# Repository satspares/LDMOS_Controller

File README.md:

# LDMOS_Controller
LDMOS Controller with DWIN Display
New October 2026

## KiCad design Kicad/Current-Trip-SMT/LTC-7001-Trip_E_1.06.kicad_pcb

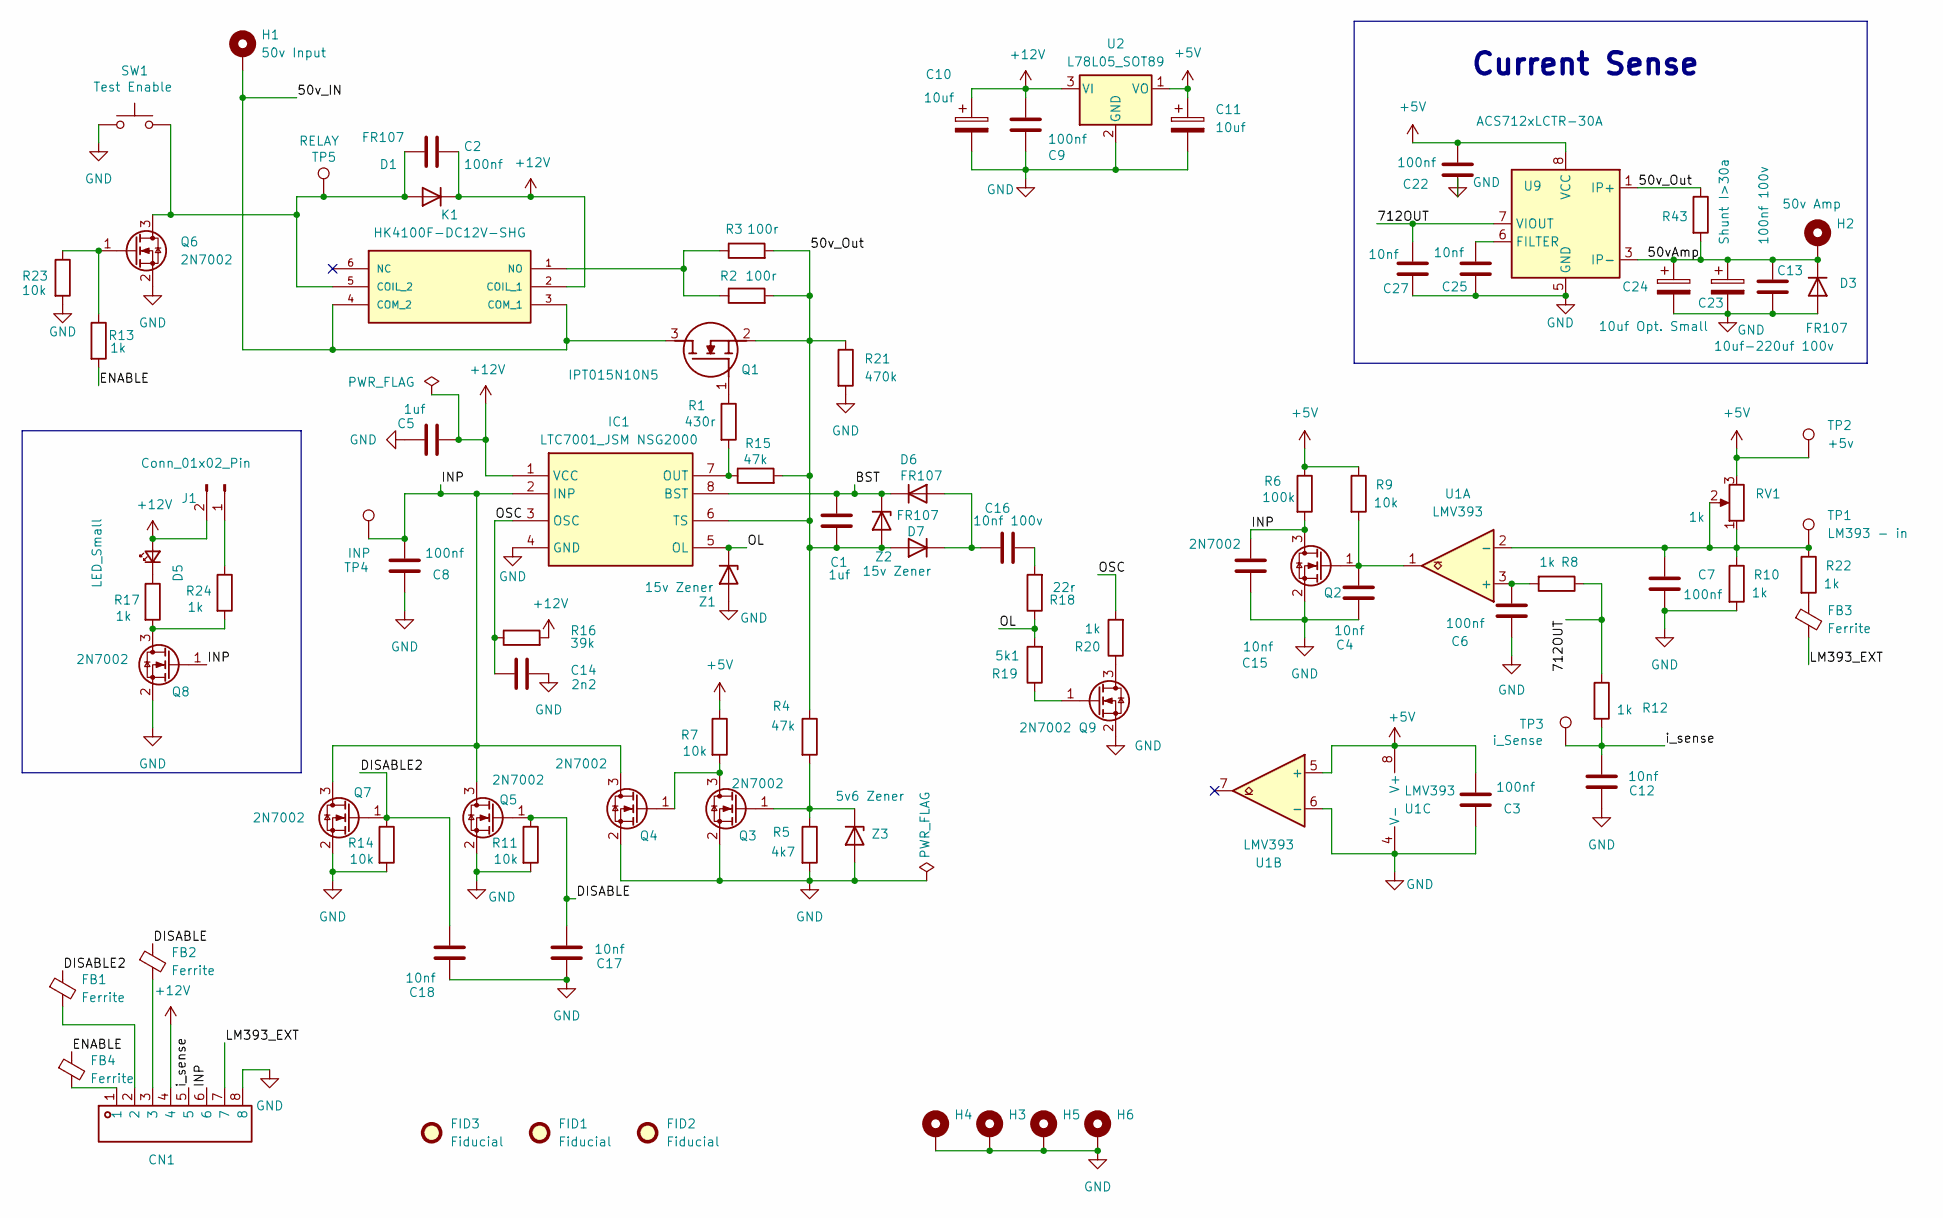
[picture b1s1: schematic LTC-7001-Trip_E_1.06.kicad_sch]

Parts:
C1, C5: 1uf; R_1206_3216Metric_Pad1.30x1.75mm_HandSolder
C2, C3, C6, C7, C8, C9, C22: 100nf; R_1206_3216Metric_Pad1.30x1.75mm_HandSolder
C4, C12, C15, C17, C18, C25, C27: 10nf; R_1206_3216Metric_Pad1.30x1.75mm_HandSolder
C10, C11: 10uf; R_1206_3216Metric_Pad1.30x1.75mm_HandSolder
C13: 100nf 100v; R_1206_3216Metric_Pad1.30x1.75mm_HandSolder
C14: 2n2; R_1206_3216Metric_Pad1.30x1.75mm_HandSolder
C16: 10nf 100v; R_1206_3216Metric_Pad1.30x1.75mm_HandSolder
C23: 10uf-220uf 100v; CP_Radial_D10.0mm_P5.00mm
C24: 10uf Opt. Small; CP_Radial_D8.0mm_P2.50mm
CN1: CONN-TH_8P-P2.54_KF141R-2.54-8P; Manufacturer Part KF141R-2.54-8P; LCSC Part Name 1x6P 2.54mm 每排P数:8 排数:1
D1, D3, D6, D7: FR107; D_SOD-123F-Mod
D5: LED_Small; LED_D3.0mm
FB1, FB2, FB3, FB4: Ferrite; R_1206_3216Metric_Pad1.30x1.75mm_HandSolder
FID1, FID2, FID3: Fiducial; Fiducial_0.75mm_Mask1.5mm
H1: 50v Input; Power-Pad
H2: 50v Amp; Power-Pad
H3, H4, H5, H6: MountingHole_Pad; MountingHole_3.5mm_Pad_Via
IC1: LTC7001_JSM NSG2000; SOIC-8_3.9x4.9mm_P1.27mm; Manufacturer_Part_Number JSMSEMI LTC7001IMSE-JSM
J1: Conn_01x02_Pin; JST_EH_B2B-EH-A_1x02_P2.50mm_Vertical
K1: HK4100F-DC12V-SHG; HK4100FDC5VSHG; MANUFACTURER_PART_NUMBER HK4100F-DC5V-SHG
Q1: IPT015N10N5; IPT015N10N5ATMA1; Manufacturer_Part_Number IPT015N10N5; Mouser Part Number 726-IPT015N10N5ATMA1
Q2, Q3, Q4, Q5, Q6, Q7, Q8, Q9: 2N7002; SOT-23-Mod2
R1: 430r; R_1206_3216Metric_Pad1.30x1.75mm_HandSolder
R2, R3: 100r; RESC11050X120N_Mod
R4, R15: 47k; R_1206_3216Metric_Pad1.30x1.75mm_HandSolder
R5: 4k7; R_1206_3216Metric_Pad1.30x1.75mm_HandSolder
R6: 100k; R_1206_3216Metric_Pad1.30x1.75mm_HandSolder
R7, R9, R11, R14, R23: 10k; R_1206_3216Metric_Pad1.30x1.75mm_HandSolder
R8, R10, R12, R13, R17, R20, R22, R24: 1k; R_1206_3216Metric_Pad1.30x1.75mm_HandSolder
R16: 39k; R_1206_3216Metric_Pad1.30x1.75mm_HandSolder
R18: 22r; R_1206_3216Metric_Pad1.30x1.75mm_HandSolder
R19: 5k1; R_1206_3216Metric_Pad1.30x1.75mm_HandSolder
R21: 470k; R_1206_3216Metric_Pad1.30x1.75mm_HandSolder
R43: Shunt I>30a; RESC11050X120N-hole
RV1: 1k; Potentiometer_Bourns_3266W_Vertical
SW1: Test Enable; SW_PUSH_6mm
TP1: LM393 - in; TestPoint_THTPad_3.0x3.0mm_Drill1.5mm
TP2: +5v; TestPoint_THTPad_3.0x3.0mm_Drill1.5mm
TP3: i_Sense; TestPoint_THTPad_3.0x3.0mm_Drill1.5mm
TP4: INP; TestPoint_THTPad_3.0x3.0mm_Drill1.5mm
TP5: RELAY; TestPoint_THTPad_3.0x3.0mm_Drill1.5mm
U1: LMV393; SOP-8_3.76x4.96mm_P1.27mm
U2: L78L05_SOT89; SOT-89-3_Handsoldering
U9: ACS712xLCTR-30A; SOIC-8_3.9x4.9mm_P1.27mm
Z1, Z2: 15v Zener; D_SOD-123F-Mod
Z3: 5v6 Zener; D_SOD-123F-Mod

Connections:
+5V: C3.2, C11.1, C22.1, R6.1, R7.1, R9.1, RV1.3, TP2.1 (1_1), U1.5 (+), U1.8 (V+), U2.1 (VO), U9.8 (VCC)
+12V: C2.2, C5.2, C9.2, C10.1, CN1.4, D1.1 (K), D5.2 (A), IC1.1 (VCC), J1.2, K1.2 (COIL_1), R16.2, U2.3 (VI)
/50vAmp: C13.1, C23.1, C24.1, D3.1 (K), H2.1 (1_1), R43.2, U9.3 (IP-), U9.4 (IP-)
/50v_IN: H1.1 (1_1), K1.3 (COM_1), K1.4 (COM_2), Q1.3 (S)
/50v_Out: C1.2, D7.2 (A), IC1.6 (TS), Q1.2 (D), R2.2, R3.2, R4.1, R15.2, R21.1, R43.1, U9.1 (IP+), U9.2 (IP+), Z2.2 (A)
/712OUT: C27.1, R8.1, R12.1, U9.7 (VIOUT)
/BST: C1.1, D6.1 (K), IC1.8 (BST), Z2.1 (K)
/DISABLE: C17.2, FB2.1, Q5.1 (G), R11.1
/DISABLE2: C18.2, FB1.1, Q7.1 (G), R14.1
/ENABLE: FB4.1, R13.2
/INP: C8.2, C15.1, CN1.6, IC1.2 (INP), Q2.3 (D), Q4.3 (D), Q5.3 (D), Q7.3 (D), Q8.1 (G), R6.2, TP4.1 (1_1)
/LM393_EXT: CN1.7, FB3.2
/OL: IC1.5 (OL), R18.1, R19.2, Z1.1 (K)
/OSC: C14.1, IC1.3 (OSC), R16.1, R20.2
/i_sense: C12.1, CN1.5, R12.2, TP3.1 (1_1)
GND: C3.1, C4.1, C5.1, C6.1, C7.1, C8.1, C9.1, C10.2, C11.2, C12.2, C13.2, C14.2, C15.2, C17.1, C18.1, C22.2, C23.2, C24.2, C25.1, C27.2, CN1.8, D3.2 (A), H3.1 (1_1), H4.1 (1_1), H5.1 (1_1), H6.1 (1_1), IC1.4 (GND), Q2.2 (S), Q3.2 (S), Q4.2 (S), Q5.2 (S), Q6.2 (S), Q7.2 (S), Q8.2 (S), Q9.2 (S), R5.2, R10.2, R11.2, R14.2, R21.2, R23.2, SW1.1, U1.4 (V-), U1.6 (-), U2.2 (GND), U9.5 (GND), Z1.2 (A), Z3.2 (A)
unnamed: C16.2, R18.2
unnamed: CN1.1, FB4.2
unnamed: CN1.2, FB1.2
unnamed: CN1.3, FB2.2
unnamed: C2.1, D1.2 (A), K1.5 (COIL_2), Q6.3 (D), SW1.2, TP5.1 (1_1)
unnamed: D5.1 (K), R17.1
unnamed: C16.1, D6.2 (A), D7.1 (K)
unnamed: FB3.1, R22.2
unnamed: IC1.7 (OUT), R1.2, R15.1
unnamed: J1.1, R24.1
unnamed: K1.1 (NO), R2.1, R3.1
unnamed: Q1.1 (G), R1.1
unnamed: C4.2, Q2.1 (G), R9.2, U1.1
unnamed: Q3.3 (D), Q4.1 (G), R7.2
unnamed: Q3.1 (G), R4.2, R5.1, Z3.1 (K)
unnamed: Q6.1 (G), R13.1, R23.1
unnamed: Q8.3 (D), R17.2, R24.2
unnamed: Q9.3 (D), R20.1
unnamed: Q9.1 (G), R19.1
unnamed: C6.2, R8.2, U1.3 (+)
unnamed: C7.2, R10.1, R22.1, RV1.1, RV1.2, TP1.1 (1_1), U1.2 (-)
unnamed: C25.2, U9.6 (FILTER)

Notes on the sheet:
Current Sense

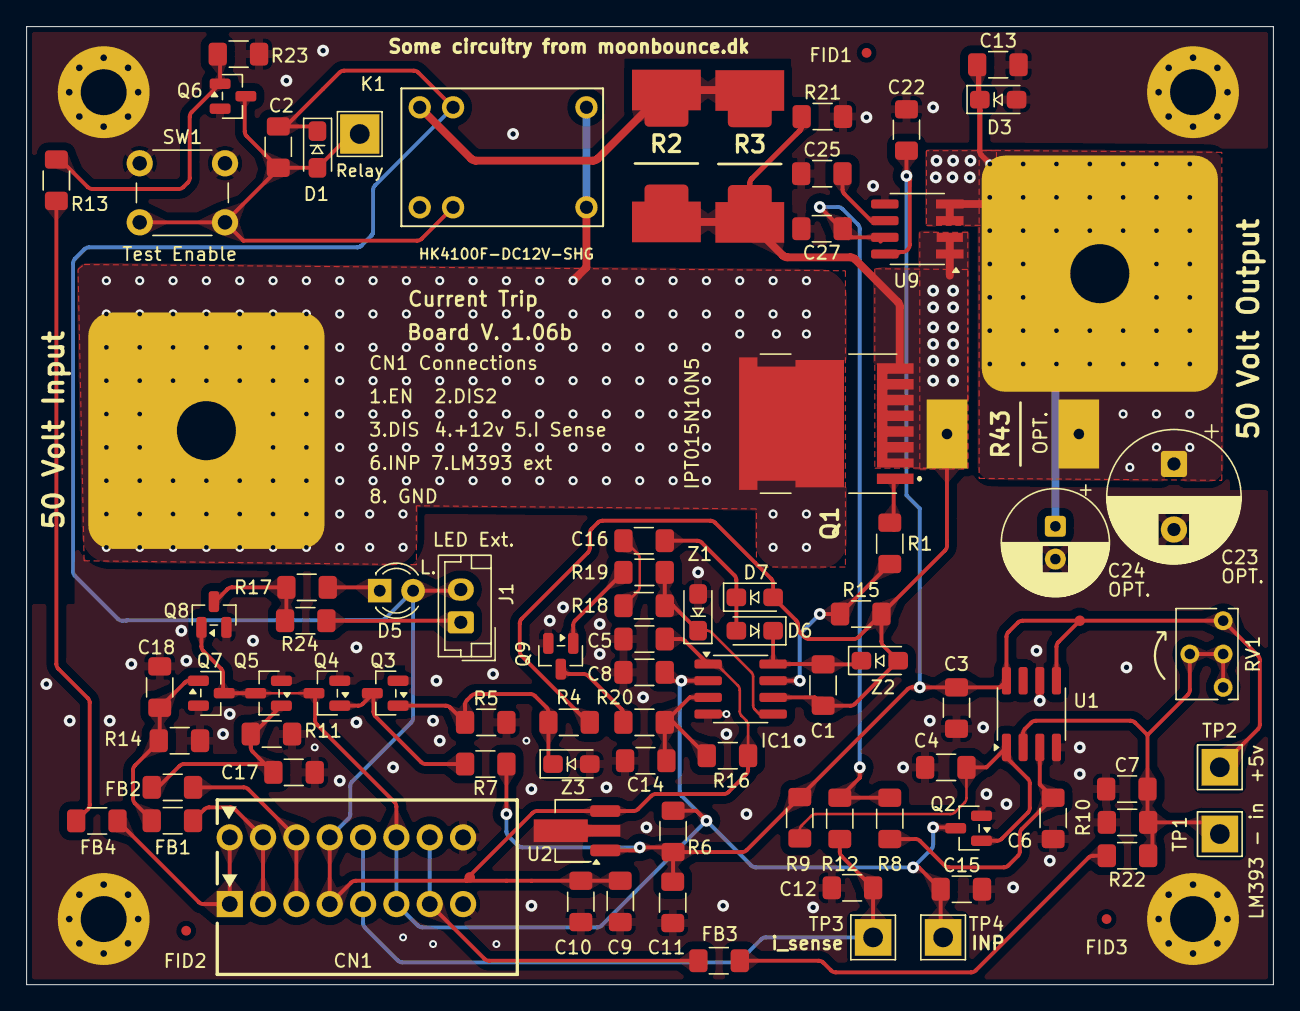
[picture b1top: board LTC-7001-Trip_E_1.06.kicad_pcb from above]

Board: 2 copper layers, 95.0 x 73.0 mm, 92 parts (0 on the bottom side), 38 nets.

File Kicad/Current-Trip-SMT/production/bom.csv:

Designator,Footprint,Quantity,Value,LCSC Part #
"C1, C5",1206,2,1uf,
"C10, C11",1206,2,10uf,
"C12, C15, C17, C18, C25, C27, C4",1206,7,10nf,
C13,1206,1,100nf 100v,
C14,1206,1,2n2,
C16,1206,1,10nf 100v,
"C2, C22, C3, C6, C7, C8, C9",1206,7,100nf,
C23,CP_Radial_D10.0mm_P5.00mm,1,10uf-220uf 100v,
C24,CP_Radial_D8.0mm_P2.50mm,1,10uf Opt. Small,
CN1,CONN-TH_8P-P2.54_KF141R-2.54-8P,1,~,
"D1, D3, D6, D7",D_SOD-123F-Mod,4,FR107,
D5,LED_D3.0mm,1,LED_Small,
"FB1, FB2, FB3, FB4",1206,4,Ferrite,
IC1,SOIC-8_3.9x4.9mm_P1.27mm,1,LTC7001_JSM NSG2000,
J1,JST_EH_B2B-EH-A_1x02_P2.50mm_Vertical,1,Conn_01x02_Pin,
K1,HK4100FDC5VSHG,1,HK4100F-DC12V-SHG,
Q1,IPT015N10N5ATMA1,1,IPT015N10N5,
"Q2, Q3, Q4, Q5, Q6, Q7, Q8, Q9",SOT-23-Mod2,8,2N7002,
R1,1206,1,430r,
"R10, R12, R13, R17, R20, R22, R24, R8",1206,8,1k,
"R11, R14, R23, R7, R9",1206,5,10k,
"R15, R4",1206,2,47k,
R16,1206,1,39k,
R18,1206,1,22r,
R19,1206,1,5k1,
"R2, R3",RESC11050X120N_Mod,2,100r,
R21,1206,1,470k,
R43,RESC11050X120N-hole,1,Shunt I>30a,
R5,1206,1,4k7,
R6,1206,1,100k,
RV1,Potentiometer_Bourns_3266W_Vertical,1,1k,
SW1,SW_PUSH_6mm,1,Test Enable,
TP1,TestPoint_THTPad_3.0x3.0mm_Drill1.5mm,1,LM393 - in,
TP2,TestPoint_THTPad_3.0x3.0mm_Drill1.5mm,1,+5v,
TP3,TestPoint_THTPad_3.0x3.0mm_Drill1.5mm,1,i_Sense,
TP4,TestPoint_THTPad_3.0x3.0mm_Drill1.5mm,1,INP,
TP5,TestPoint_THTPad_3.0x3.0mm_Drill1.5mm,1,RELAY,
U1,SOP-8_3.76x4.96mm_P1.27mm,1,LMV393,
U2,SOT-89-3_Handsoldering,1,L78L05_SOT89,
U9,SOIC-8_3.9x4.9mm_P1.27mm,1,ACS712xLCTR-30A,
"Z1, Z2",D_SOD-123F-Mod,2,15v Zener,
Z3,D_SOD-123F-Mod,1,5v6 Zener,

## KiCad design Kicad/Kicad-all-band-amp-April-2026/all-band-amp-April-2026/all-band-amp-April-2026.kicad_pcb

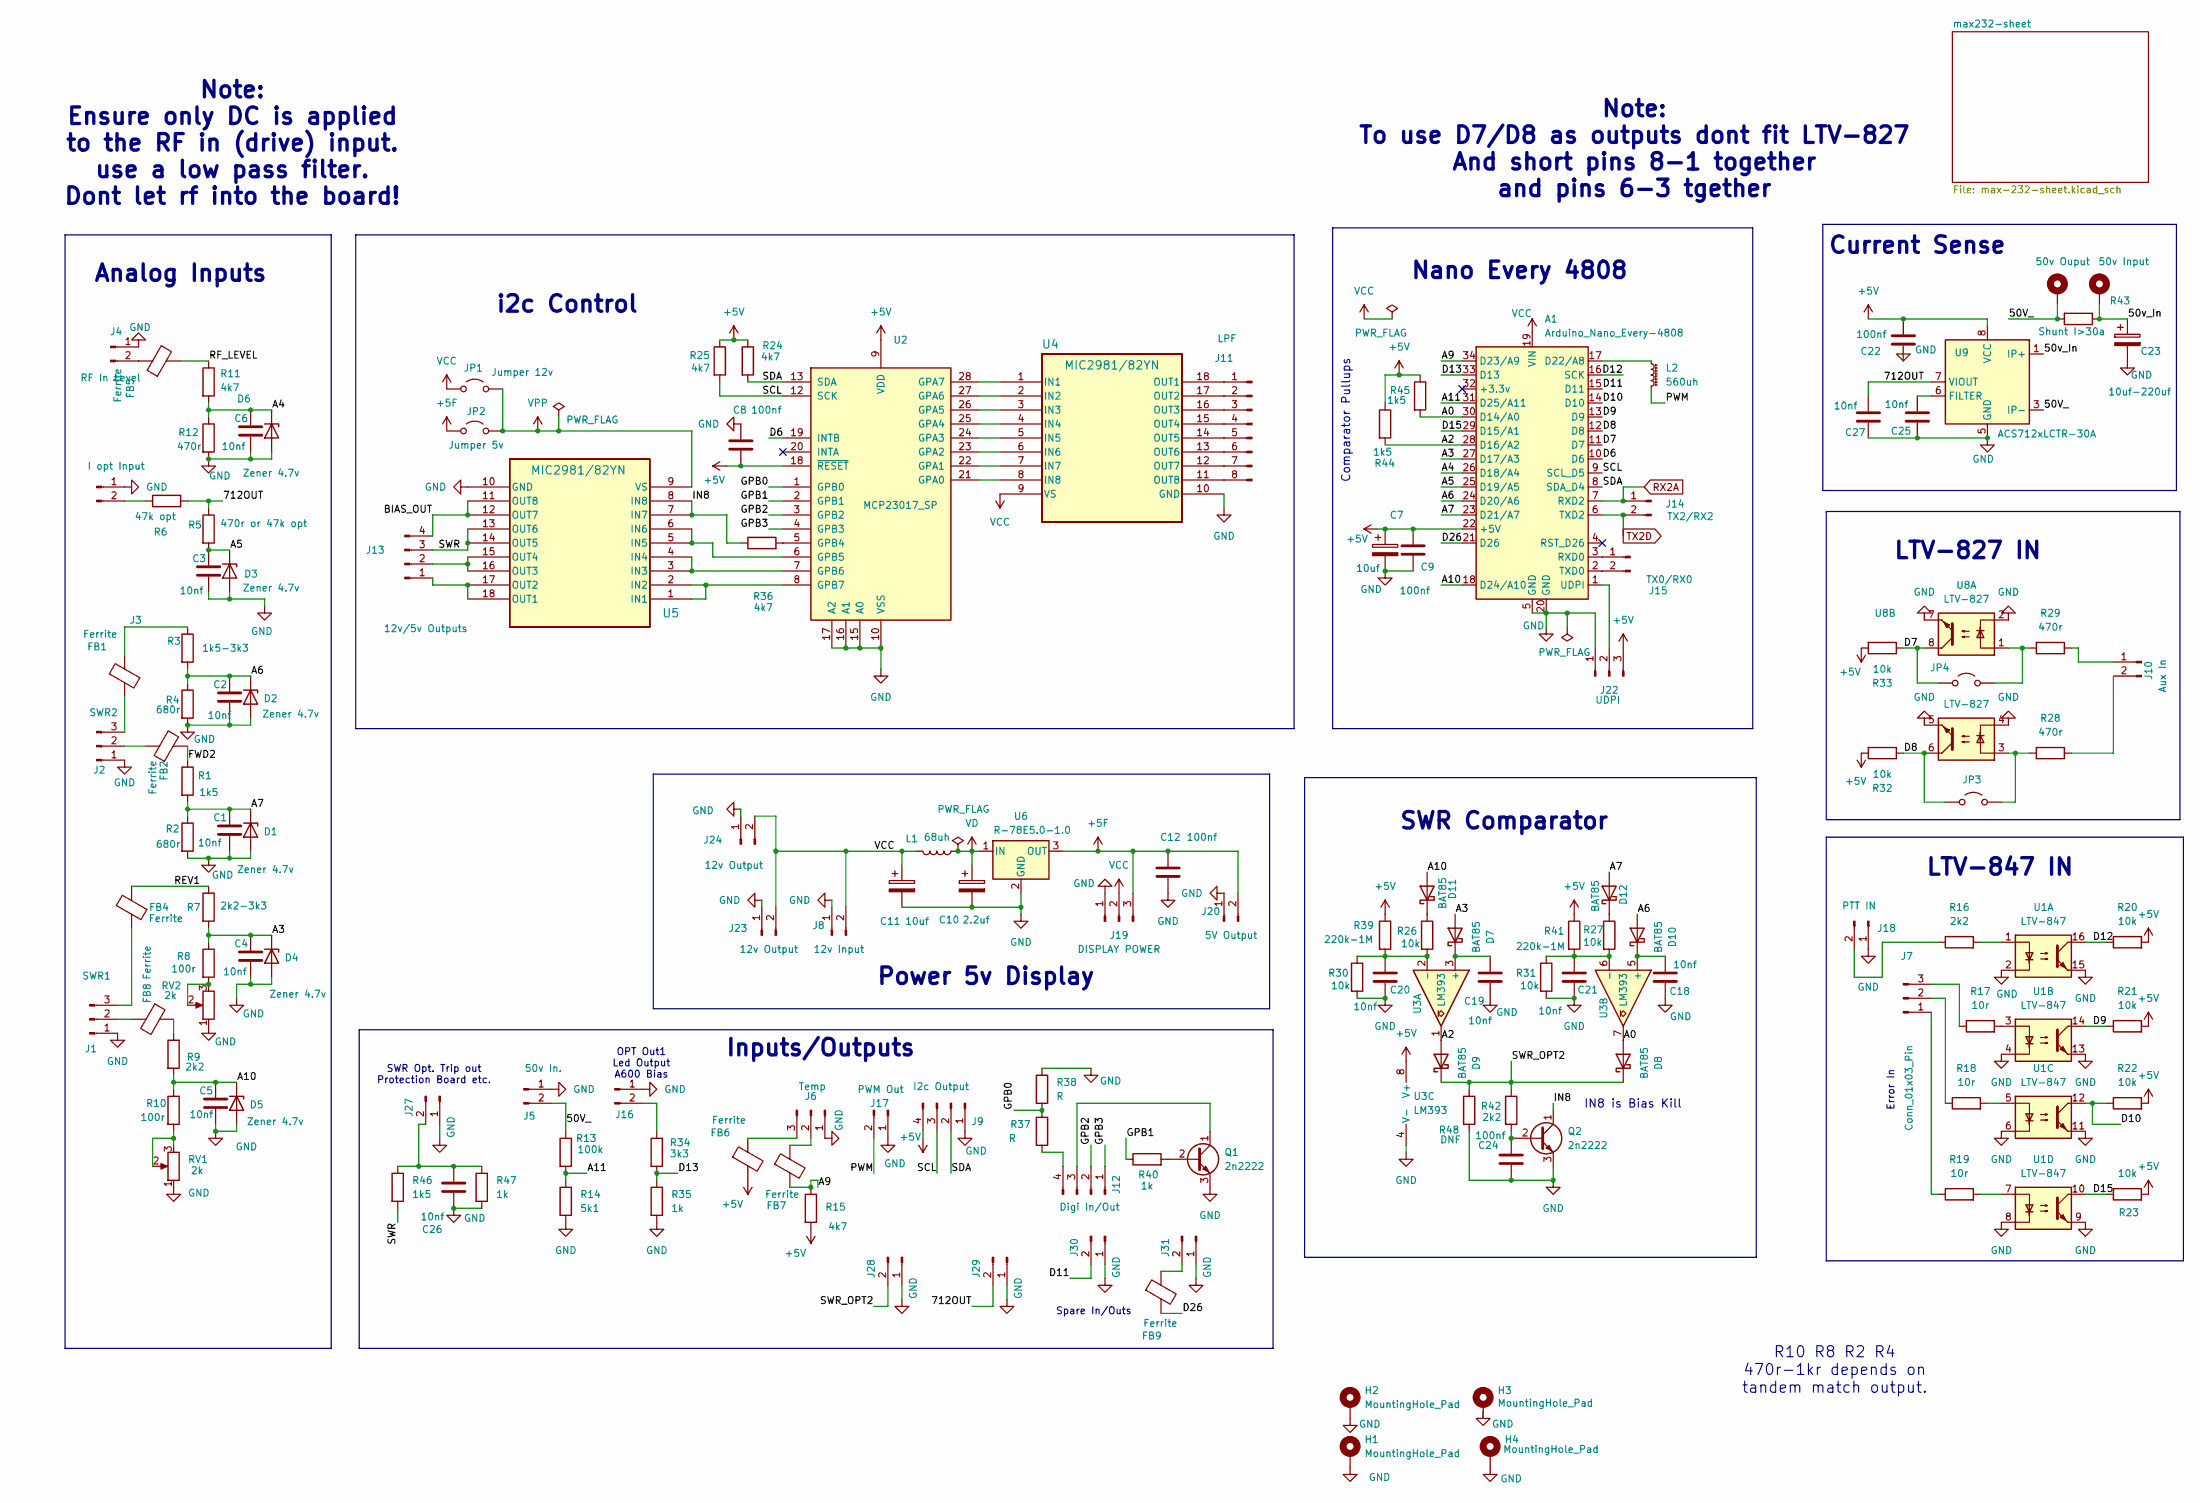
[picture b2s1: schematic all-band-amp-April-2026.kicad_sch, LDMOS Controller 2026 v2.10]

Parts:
A1: Arduino_Nano_Every-4808; DIP-34_W15.24mm
C1, C2, C3, C4, C5, C6, C18, C19, C20, C21, C25, C26, C27: 10nf; C_Disc_D3.4mm_W2.1mm_P2.50mm
C7, C11: 10uf; CP_Radial_D5.0mm_P2.00mm
C8, C9, C12, C22, C24: 100nf; C_Disc_D6.0mm_W2.5mm_P5.00mm
C10: 2.2uf; CP_Radial_D5.0mm_P2.00mm
C23: 10uf-220uf; CP_Radial_D10.0mm_P5.00mm
D1, D2, D3, D4, D5, D6: Zener 4.7v; D_DO-35_SOD27_P7.62mm_Horizontal
D7, D8, D9, D10, D11, D12: BAT85; D_DO-35_SOD27_P7.62mm_Horizontal
FB1, FB2, FB4, FB5, FB6, FB7, FB8, FB9: Ferrite; R_1206_3216Metric_Pad1.30x1.75mm_HandSolder-mod
H1, H2, H3, H4: MountingHole_Pad; MountingHole_3.5mm_Pad_Via
H5: 50v Ouput; PowerPad9mm
H6: 50v Input; PowerPad9mm
J1: SWR1; JST_EH_B3B-EH-A_1x03_P2.50mm_Vertical-mod2
J2: SWR2; JST_EH_B3B-EH-A_1x03_P2.50mm_Vertical-mod2
J3: I opt Input; JST_EH_B2B-EH-A_1x02_P2.50mm_Vertical-Mod
J4: RF In Level; JST_EH_B2B-EH-A_1x02_P2.50mm_Vertical-Mod
J5, J16: 50v In.; JST_EH_B2B-EH-A_1x02_P2.50mm_Vertical-Mod
J6: Temp; JST_EH_B3B-EH-A_1x03_P2.50mm_Vertical-mod2
J7: Conn_01x03_Pin; JST_EH_B3B-EH-A_1x03_P2.50mm_Vertical-mod2
J8: 12v Input; JST_EH_B2B-EH-A_1x02_P2.50mm_Vertical-Mod
J9: I2c Output; JST_EH_B4B-EH-A_1x04_P2.50mm_Vertical-mod2
J10: Aux In; JST_EH_B2B-EH-A_1x02_P2.50mm_Vertical-Mod
J11: LPF; JST_EH_B8B-EH-A_1x08_P2.50mm_Vertical
J12: Digi In/Out; JST_EH_B4B-EH-A_1x04_P2.50mm_Vertical-mod2
J13: 12v/5v Outputs; JST_EH_B4B-EH-A_1x04_P2.50mm_Vertical-mod2
J14: TX2/RX2; JST_EH_B2B-EH-A_1x02_P2.50mm_Vertical-Mod
J15: TX0/RX0; JST_EH_B2B-EH-A_1x02_P2.50mm_Vertical-Mod
J17: PWM Out; JST_EH_B2B-EH-A_1x02_P2.50mm_Vertical-Mod
J18: PTT IN; JST_EH_B2B-EH-A_1x02_P2.50mm_Vertical-Mod
J19: DISPLAY POWER; JST_EH_B3B-EH-A_1x03_P2.50mm_Vertical-mod2
J20: 5V Output; JST_EH_B2B-EH-A_1x02_P2.50mm_Vertical-Mod
J22: UDPI; JST_EH_B3B-EH-A_1x03_P2.50mm_Vertical
J23, J24: 12v Output; JST_EH_B2B-EH-A_1x02_P2.50mm_Vertical-Mod
J27, J28, J29, J30, J31: SWR trip out; JST_EH_B2B-EH-A_1x02_P2.50mm_Vertical-Mod
JP1: Jumper 12v; SolderWire-0.5sqmm_1x02_P4.8mm_D0.9mm_OD2.3mm
JP2: Jumper 5v; SolderWire-0.5sqmm_1x02_P4.8mm_D0.9mm_OD2.3mm
JP3, JP4: Jumper_2_Open; SolderJumper-2_P1.3mm_Open_TrianglePad1.0x1.5mm
L1: 68uh; L_Radial_D7.0mm_P3.00mm
L2: 560uh; L_Axial_L5.3mm_D2.2mm_P7.62mm_Horizontal_Vishay_IM-1
Q1, Q2: 2n2222; TO-92_HandSolder
R1, R44, R45, R46: 1k5; R_Axial_DIN0207_L6.3mm_D2.5mm_P7.62mm_Horizontal
R2, R4: 680r; R_Axial_DIN0207_L6.3mm_D2.5mm_P7.62mm_Horizontal
R3: 1k5-3k3; R_Axial_DIN0207_L6.3mm_D2.5mm_P7.62mm_Horizontal
R5: 470r or 47k opt; R_Axial_DIN0207_L6.3mm_D2.5mm_P7.62mm_Horizontal
R6: 47k opt; R_Axial_DIN0207_L6.3mm_D2.5mm_P7.62mm_Horizontal
R7: 2k2-3k3; R_Axial_DIN0207_L6.3mm_D2.5mm_P7.62mm_Horizontal
R8, R10: 100r; R_Axial_DIN0207_L6.3mm_D2.5mm_P7.62mm_Horizontal
R9, R16, R42: 2k2; R_Axial_DIN0207_L6.3mm_D2.5mm_P7.62mm_Horizontal
R11, R15, R24, R25, R36: 4k7; R_Axial_DIN0207_L6.3mm_D2.5mm_P7.62mm_Horizontal
R12, R28, R29: 470r; R_Axial_DIN0207_L6.3mm_D2.5mm_P7.62mm_Horizontal
R13: 100k; R_Axial_DIN0207_L6.3mm_D2.5mm_P7.62mm_Horizontal
R14: 5k1; R_Axial_DIN0207_L6.3mm_D2.5mm_P7.62mm_Horizontal
R17, R18, R19: 10r; R_Axial_DIN0207_L6.3mm_D2.5mm_P7.62mm_Horizontal
R20, R21, R22, R23, R26, R27, R30, R31, R32, R33: 10k; R_Axial_DIN0207_L6.3mm_D2.5mm_P7.62mm_Horizontal
R34: 3k3; R_Axial_DIN0207_L6.3mm_D2.5mm_P7.62mm_Horizontal
R35, R40, R47: 1k; R_Axial_DIN0207_L6.3mm_D2.5mm_P7.62mm_Horizontal
R37, R38: R; R_Axial_DIN0207_L6.3mm_D2.5mm_P7.62mm_Horizontal
R39, R41: 220k-1M; R_Axial_DIN0207_L6.3mm_D2.5mm_P7.62mm_Horizontal
R43: Shunt I>30a; CHSA3920R0003F-MOD
R48: DNF; R_Axial_DIN0207_L6.3mm_D2.5mm_P7.62mm_Horizontal
RV1, RV2: 2k; Potentiometer_Bourns_3299Y_Vertical
U1: LTV-847; DIP-16_W7.62mm
U2: MCP23017_SP; DIP-28_W7.62mm
U3: LM393; DIP-8_W7.62mm
U4, U5: MIC2981/82YN; DIP-18_W7.62mm_Socket
U6: R-78E5.0-1.0; Converter_DCDC_RECOM_R-78E-0.5_THT
U8: LTV-827; DIP-8_W7.62mm
U9: ACS712xLCTR-30A; SOIC-8_3.9x4.9mm_P1.27mm

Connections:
+5F: C12.1, J19.3, J20.2, JP2.1 (A), U6.3 (OUT); also elsewhere on the board
+5V: A1.22 (+5V), C7.1, C8.2, C9.1, C22.1, FB6.2, J9.4, J22.3, R15.2, R20.2, R21.2, R22.2, R23.2, R24.1, R25.1, R32.2, R33.2, R39.1, R41.1, R44.1, R45.1, U2.9 (VDD), U2.18 (~RESET), U3.8 (V+), U9.8 (VCC)
/50V_: H5.1 (1_1), J5.2, R13.1, R43.2, U9.3 (IP-), U9.4 (IP-)
/50v_In: C23.1, H6.1 (1_1), R43.1, U9.1 (IP+), U9.2 (IP+)
/712OUT: C27.1, J29.2, R5.1, R6.2, U9.7 (VIOUT)
/A0: A1.30 (D14/A0), D8.2 (A), R45.2, U3.7
/A2: A1.28 (D16/A2), D9.2 (A), R44.2, U3.1
/A3: A1.27 (D17/A3), C4.1, D4.1 (K), D7.2 (A), R7.2, R8.1
/A4: A1.26 (D18/A4), C6.1, D6.1 (K), R11.2, R12.1
/A5: A1.25 (D19/A5), C3.1, D3.1 (K), R5.2
/A6: A1.24 (D20/A6), C2.1, D2.1 (K), D10.2 (A), R3.2, R4.1
/A7: A1.23 (D21/A7), C1.1, D1.1 (K), D12.2 (A), R1.2, R2.1
/A9: A1.34 (D23/A9), FB7.2, R15.1
/A10: A1.18 (D24/A10), C5.1, D5.1 (K), D11.2 (A), R9.2, R10.1
/A11: A1.31 (D25/A11), R13.2, R14.1
/BIAS_OUT: J13.4, U5.11 (OUT8), U5.12 (OUT7)
/D6: A1.10 (D6), U2.19 (INTB)
/D7: A1.11 (D7), JP4.1 (A), R33.1, U8.8
/D8: A1.12 (D8), JP3.1 (A), R32.1, U8.6
/D9: A1.13 (D9), R21.1, U1.14
/D10: A1.14 (D10), R22.1, U1.12
/D11: A1.15 (D11), J30.2
/D12: A1.16 (SCK), R20.1, U1.16
/D13: A1.33 (D13), R34.2, R35.1
/D15: A1.29 (D15/A1), R23.1, U1.10
/D26: A1.21 (D26), FB9.2
/FWD2: FB2.2, R1.1
/GPB0: R37.1, R38.2, U2.1 (GPB0)
/GPB1: R40.1, U2.2 (GPB1)
/GPB2: J12.2, U2.3 (GPB2)
/GPB3: J12.1, U2.4 (GPB3)
/IN8: Q2.1 (C), R36.1, U5.7 (IN7), U5.8 (IN8)
/PWM: J17.2, L2.2
/REV1: FB4.2, R7.1
/RF_LEVEL: FB5.2, R11.1
/SCL: A1.9 (SCL_D5), J9.3, R25.2, U2.12 (SCK)
/SDA: A1.8 (SDA_D4), J9.2, R24.2, U2.13 (SDA)
/SWR: J13.3, R46.2, U5.13 (OUT6), U5.14 (OUT5)
/SWR_OPT2: D8.1 (K), D9.1 (K), J28.2, R42.1, R48.1
GND: A1.5 (GND), A1.20 (GND), C1.2, C2.2, C3.2, C4.2, C5.2, C6.2, C7.2, C8.1, C9.2, C10.2, C11.2, C12.2, C18.1, C19.2, C20.2, C21.2, C22.2, C23.2, C24.2, C25.1, C26.2, C27.2, D1.2 (A), D2.2 (A), D3.2 (A), D4.2 (A), D5.2 (A), D6.2 (A), H1.1 (1_1), H2.1 (1_1), H3.1 (1_1), H4.1 (1_1), J1.1, J2.1, J3.1, J4.1, J5.1, J6.1, J8.1, J9.1, J16.1, J17.1, J18.1, J19.1, J20.1, J22.1, J23.1, J24.1, J27.1, J28.1, J29.1, J30.1, J31.1, Q1.3 (E), Q2.3 (E), R2.2, R4.2, R12.2, R14.2, R30.2, R31.2, R35.2, R38.1, R47.2, R48.2, RV1.1, RV2.1, U1.2, U1.4, U1.6, U1.8, U1.9, U1.11, U1.13, U1.15, U2.10 (VSS), U2.15 (A0), U2.16 (A1), U2.17 (A2), U3.4 (V-), U4.10 (GND), U5.10 (GND), U6.2 (GND), U8.2, U8.4, U8.5, U8.7, U9.5 (GND); also elsewhere on the board
unnamed: A1.17 (D22/A8), L2.1
unnamed: A1.3 (RXD0), J15.1
unnamed: A1.2 (TXD0), J15.2
unnamed: A1.1 (UDPI), J22.2
unnamed: C19.1, D7.1 (K), U3.3 (+)
unnamed: C18.2, D10.1 (K), U3.5 (+)
unnamed: D11.1 (K), R26.1
unnamed: D12.1 (K), R27.1
unnamed: FB1.1, R3.1
unnamed: FB8.1, R9.1
unnamed: FB8.2, J1.2
unnamed: FB4.1, J1.3
unnamed: FB2.1, J2.2
unnamed: FB1.2, J2.3
unnamed: J3.2, R6.1
unnamed: FB5.1, J4.2
unnamed: FB7.1, J6.2
unnamed: FB6.1, J6.3
unnamed: J7.1, R19.1
unnamed: J7.2, R18.1
unnamed: J7.3, R17.1
unnamed: J10.1, R29.1
unnamed: J10.2, R28.1
unnamed: J11.1, U4.18 (OUT1)
unnamed: J11.2, U4.17 (OUT2)
unnamed: J11.3, U4.16 (OUT3)
unnamed: J11.4, U4.15 (OUT4)
unnamed: J11.5, U4.14 (OUT5)
unnamed: J11.6, U4.13 (OUT6)
unnamed: J11.7, U4.12 (OUT7)
unnamed: J11.8, U4.11 (OUT8)
unnamed: J12.3, Q1.1 (C)
unnamed: J12.4, R37.2
unnamed: J13.1, U5.17 (OUT2), U5.18 (OUT1)
unnamed: J13.2, U5.15 (OUT4), U5.16 (OUT3)
unnamed: J16.2, R34.1
unnamed: J18.2, R16.1
unnamed: C26.1, J27.2, R46.1, R47.1
unnamed: FB9.1, J31.2
unnamed: JP3.2 (B), R28.2, U8.3
unnamed: JP4.2 (B), R29.2, U8.1
unnamed: Q1.2 (B), R40.2
unnamed: C24.1, Q2.2 (B), R42.2
unnamed: R8.2, RV2.2, RV2.3
unnamed: R10.2, RV1.2, RV1.3
unnamed: R16.2, U1.1
unnamed: R17.2, U1.3
unnamed: R18.2, U1.5
unnamed: R19.2, U1.7
unnamed: U2.21 (GPA0), U4.8 (IN8)
unnamed: U2.22 (GPA1), U4.7 (IN7)
unnamed: U2.23 (GPA2), U4.6 (IN6)
unnamed: U2.24 (GPA3), U4.5 (IN5)
unnamed: U2.25 (GPA4), U4.4 (IN4)
unnamed: U2.26 (GPA5), U4.3 (IN3)
unnamed: U2.27 (GPA6), U4.2 (IN2)
unnamed: U2.28 (GPA7), U4.1 (IN1)
unnamed: R36.2, U2.5 (GPB4)
unnamed: U2.6 (GPB5), U5.5 (IN5), U5.6 (IN6)
unnamed: U2.7 (GPB6), U5.3 (IN3), U5.4 (IN4)
unnamed: U2.8 (GPB7), U5.1 (IN1), U5.2 (IN2)
unnamed: C20.1, R26.2, R30.1, R39.2, U3.2 (-)
unnamed: C21.1, R27.2, R31.1, R41.2, U3.6 (-)
unnamed: C25.2, U9.6 (FILTER)
RX2A: A1.7 (RXD2), J14.1; also elsewhere on the board
TX2D: A1.6 (TXD2), J14.2; also elsewhere on the board
VCC: A1.19 (VIN), C11.1, J8.2, J19.2, J23.2, J24.2, JP1.1 (A), L1.2, U4.9 (VS)
VD: C10.1, L1.1, U6.1 (IN)
VPP: JP1.2 (B), JP2.2 (B), U5.9 (VS)

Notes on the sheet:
SWR Opt. Trip out Protection Board etc.
LTV-847 IN
Note: Ensure only DC is applied to the RF in (drive) input. use a low pass filter. Dont let rf into the board!
Analog Inputs
Inputs/Outputs
Current Sense
OPT Out1 Led Output A600 Bias
Spare In/Outs
Note: To use D7/D8 as outputs dont fit LTV-827 And short pins 8-1 together and pins 6-3 tgether
Nano Every 4808
SWR Comparator
R10 R8 R2 R4 470r-1kr depends on tandem match output.
i2c Control
LTV-827 IN
Error In
IN8 is Bias Kill
Power 5v Display
Comparator Pullups

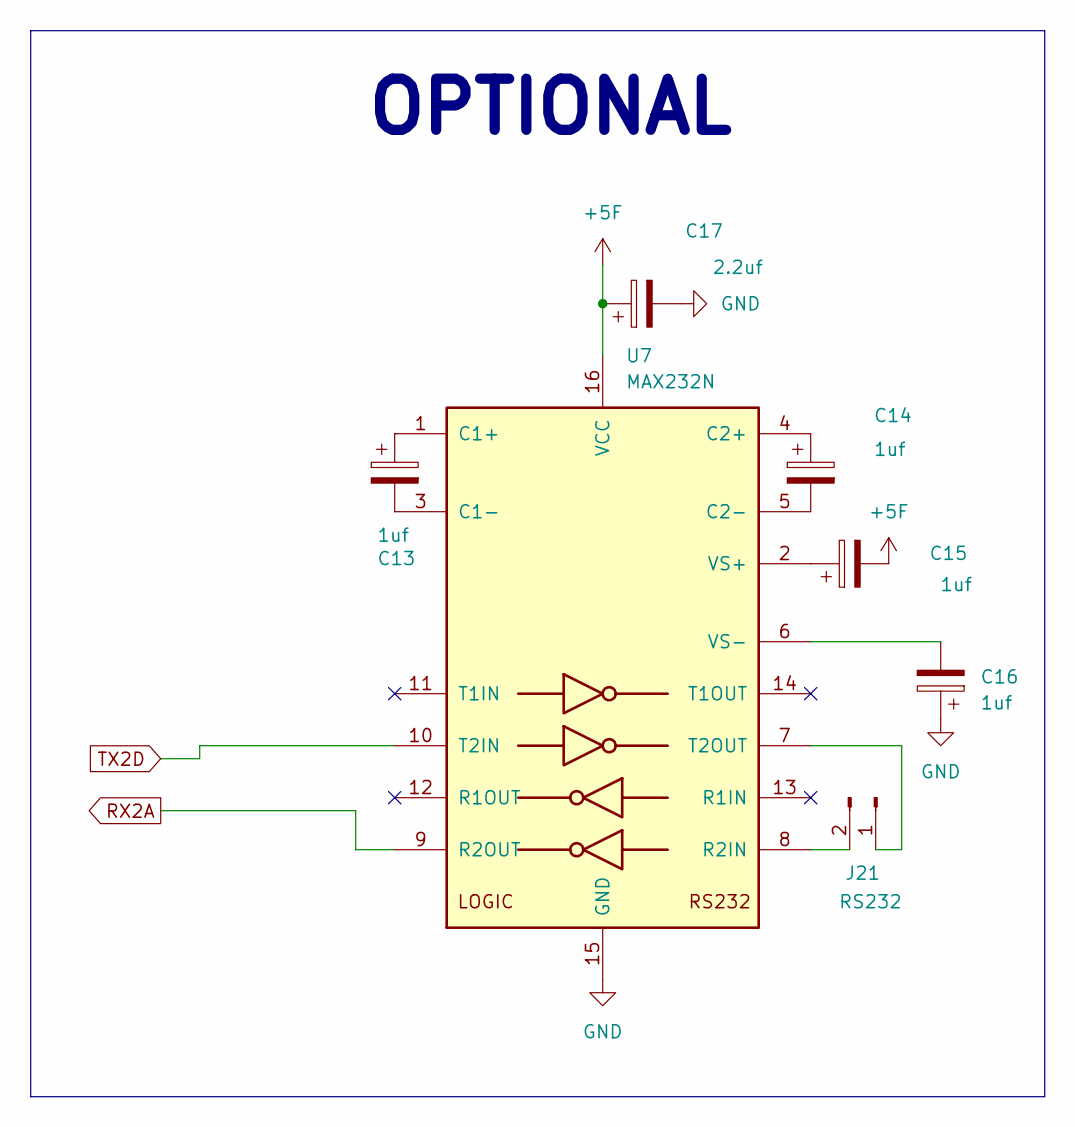
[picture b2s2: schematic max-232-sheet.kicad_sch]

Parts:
C13, C14, C15, C16: 1uf; CP_Radial_D5.0mm_P2.00mm
C17: 2.2uf; CP_Radial_D5.0mm_P2.00mm
J21: RS232; JST_EH_B2B-EH-A_1x02_P2.50mm_Vertical-Mod
U7: MAX232N; DIP-16_W7.62mm

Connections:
+5F: C15.2, C17.1, U7.16 (VCC); also elsewhere on the board
GND: C16.1, C17.2, U7.15 (GND); also elsewhere on the board
unnamed: J21.1, U7.7 (T2OUT)
unnamed: J21.2, U7.8 (R2IN)
unnamed: C13.1, U7.1 (C1+)
unnamed: C13.2, U7.3 (C1-)
unnamed: C14.1, U7.4 (C2+)
unnamed: C14.2, U7.5 (C2-)
unnamed: C15.1, U7.2 (VS+)
unnamed: C16.2, U7.6 (VS-)
RX2A: U7.9 (R2OUT); also elsewhere on the board
TX2D: U7.10 (T2IN); also elsewhere on the board

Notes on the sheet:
OPTIONAL

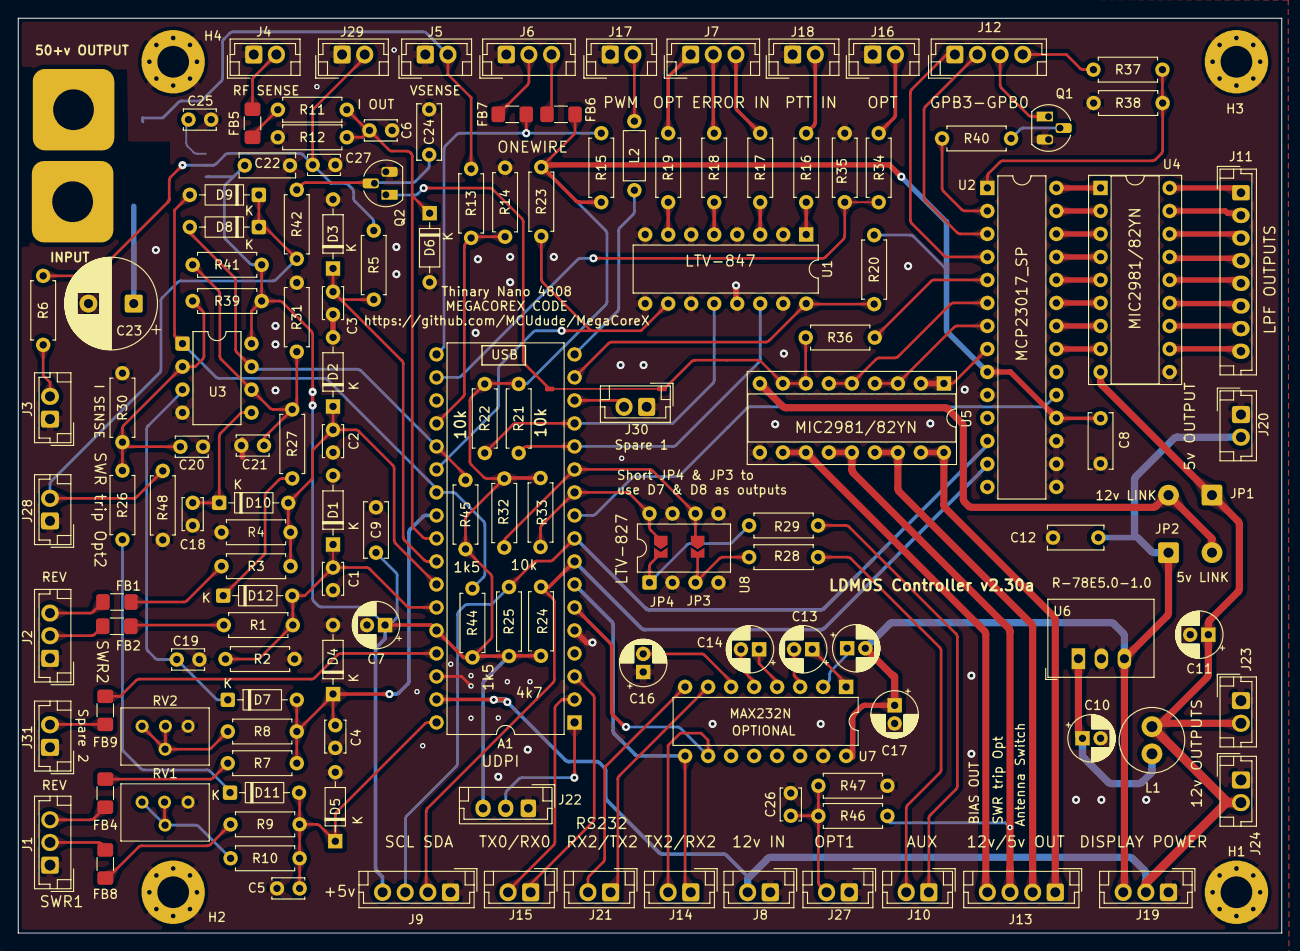
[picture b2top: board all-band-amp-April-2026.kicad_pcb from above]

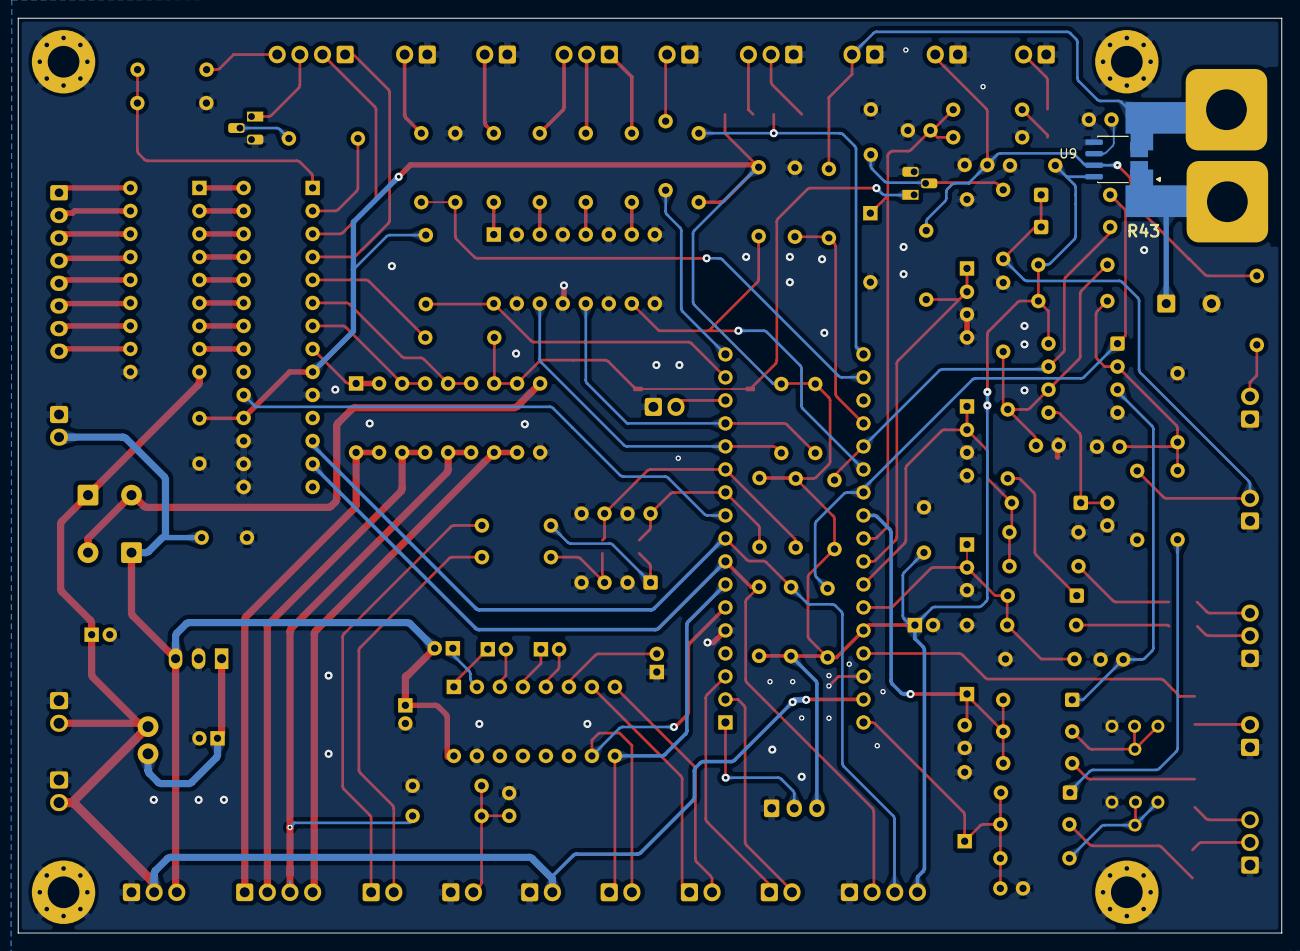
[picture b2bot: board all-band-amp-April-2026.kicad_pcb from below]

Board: 2 copper layers, 139.5 x 101.0 mm, 150 parts (2 on the bottom side), 117 nets.

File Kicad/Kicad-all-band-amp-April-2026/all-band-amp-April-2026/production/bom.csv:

Designator,Footprint,Quantity,Value,LCSC Part #
A1,DIP-34_W15.24mm,1,Arduino_Nano_Every-4808,
"C1, C18, C19, C2, C20, C21, C25, C26, C27, C3, C4, C5, C6",C_Disc_D3.4mm_W2.1mm_P2.50mm,13,10nf,
"C10, C17",CP_Radial_D5.0mm_P2.00mm,2,2.2uf,
"C11, C7",CP_Radial_D5.0mm_P2.00mm,2,10uf,
"C12, C22, C24, C8, C9",C_Disc_D6.0mm_W2.5mm_P5.00mm,5,100nf,
"C13, C14, C15, C16",CP_Radial_D5.0mm_P2.00mm,4,1uf,
C23,CP_Radial_D10.0mm_P5.00mm,1,10uf-220uf,
"D1, D2, D3, D4, D5, D6",D_DO-35_SOD27_P7.62mm_Horizontal,6,Zener 4.7v,
"D10, D11, D12, D7, D8, D9",D_DO-35_SOD27_P7.62mm_Horizontal,6,BAT85,
"FB1, FB2, FB4, FB5, FB6, FB7, FB8, FB9",1206,8,Ferrite,
J1,JST_EH_B3B-EH-A_1x03_P2.50mm_Vertical-mod2,1,SWR1,
J10,JST_EH_B2B-EH-A_1x02_P2.50mm_Vertical-Mod,1,Aux In,
J11,JST_EH_B8B-EH-A_1x08_P2.50mm_Vertical,1,LPF,
J12,JST_EH_B4B-EH-A_1x04_P2.50mm_Vertical-mod2,1,Digi In/Out,
J13,JST_EH_B4B-EH-A_1x04_P2.50mm_Vertical-mod2,1,12v/5v Outputs,
J14,JST_EH_B2B-EH-A_1x02_P2.50mm_Vertical-Mod,1,TX2/RX2,
J15,JST_EH_B2B-EH-A_1x02_P2.50mm_Vertical-Mod,1,TX0/RX0,
"J16, J5",JST_EH_B2B-EH-A_1x02_P2.50mm_Vertical-Mod,2,50v In.,
J17,JST_EH_B2B-EH-A_1x02_P2.50mm_Vertical-Mod,1,PWM Out,
J18,JST_EH_B2B-EH-A_1x02_P2.50mm_Vertical-Mod,1,PTT IN,
J19,JST_EH_B3B-EH-A_1x03_P2.50mm_Vertical-mod2,1,DISPLAY POWER,
J2,JST_EH_B3B-EH-A_1x03_P2.50mm_Vertical-mod2,1,SWR2,
J20,JST_EH_B2B-EH-A_1x02_P2.50mm_Vertical-Mod,1,5V Output,
J21,JST_EH_B2B-EH-A_1x02_P2.50mm_Vertical-Mod,1,RS232,
J22,JST_EH_B3B-EH-A_1x03_P2.50mm_Vertical,1,UDPI,
"J23, J24",JST_EH_B2B-EH-A_1x02_P2.50mm_Vertical-Mod,2,12v Output,
"J27, J28, J29, J30, J31",JST_EH_B2B-EH-A_1x02_P2.50mm_Vertical-Mod,5,SWR trip out,
J3,JST_EH_B2B-EH-A_1x02_P2.50mm_Vertical-Mod,1,I opt Input,
J4,JST_EH_B2B-EH-A_1x02_P2.50mm_Vertical-Mod,1,RF In Level,
J6,JST_EH_B3B-EH-A_1x03_P2.50mm_Vertical-mod2,1,Temp,
J7,JST_EH_B3B-EH-A_1x03_P2.50mm_Vertical-mod2,1,Conn_01x03_Pin,
J8,JST_EH_B2B-EH-A_1x02_P2.50mm_Vertical-Mod,1,12v Input,
J9,JST_EH_B4B-EH-A_1x04_P2.50mm_Vertical-mod2,1,I2c Output,
JP1,SolderWire-0.5sqmm_1x02_P4.8mm_D0.9mm_OD2.3mm,1,Jumper 12v,
JP2,SolderWire-0.5sqmm_1x02_P4.8mm_D0.9mm_OD2.3mm,1,Jumper 5v,
"JP3, JP4",SolderJumper-2_P1.3mm_Open_TrianglePad1.0x1.5mm,2,Jumper_2_Open,
L1,L_Radial_D7.0mm_P3.00mm,1,68uh,
L2,L_Axial_L5.3mm_D2.2mm_P7.62mm_Horizontal_Vishay_IM-1,1,560uh,
"Q1, Q2",TO-92_HandSolder,2,2n2222,
"R1, R44, R45, R46, R9",R_Axial_DIN0207_L6.3mm_D2.5mm_P7.62mm_Horizontal,5,1k5,
"R10, R8",R_Axial_DIN0207_L6.3mm_D2.5mm_P7.62mm_Horizontal,2,100r,
R11,R_Axial_DIN0204_L3.6mm_D1.6mm_P5.08mm_Horizontal,1,4k7,
R12,R_Axial_DIN0204_L3.6mm_D1.6mm_P5.08mm_Horizontal,1,470r,
R13,R_Axial_DIN0207_L6.3mm_D2.5mm_P7.62mm_Horizontal,1,100k,
R14,R_Axial_DIN0207_L6.3mm_D2.5mm_P7.62mm_Horizontal,1,5k1,
"R15, R24, R25",R_Axial_DIN0207_L6.3mm_D2.5mm_P7.62mm_Horizontal,3,4k7,
"R16, R42",R_Axial_DIN0207_L6.3mm_D2.5mm_P7.62mm_Horizontal,2,2k2,
"R17, R18, R19",R_Axial_DIN0207_L6.3mm_D2.5mm_P7.62mm_Horizontal,3,10r,
"R2, R4",R_Axial_DIN0207_L6.3mm_D2.5mm_P7.62mm_Horizontal,2,680r,
"R20, R21, R22, R23, R26, R27, R30, R31, R32, R33, R36",R_Axial_DIN0207_L6.3mm_D2.5mm_P7.62mm_Horizontal,11,10k,
"R28, R29",R_Axial_DIN0207_L6.3mm_D2.5mm_P7.62mm_Horizontal,2,470r,
"R3, R7",R_Axial_DIN0207_L6.3mm_D2.5mm_P7.62mm_Horizontal,2,1k5-3k3,
R34,R_Axial_DIN0207_L6.3mm_D2.5mm_P7.62mm_Horizontal,1,3k3,
"R35, R40, R47",R_Axial_DIN0207_L6.3mm_D2.5mm_P7.62mm_Horizontal,3,1k,
"R37, R38",R_Axial_DIN0207_L6.3mm_D2.5mm_P7.62mm_Horizontal,2,R,
"R39, R41",R_Axial_DIN0207_L6.3mm_D2.5mm_P7.62mm_Horizontal,2,220k-1M,
R43,CHSA3920R0003F-MOD,1,Shunt I>30a,
R48,R_Axial_DIN0207_L6.3mm_D2.5mm_P7.62mm_Horizontal,1,DNF,
R5,R_Axial_DIN0207_L6.3mm_D2.5mm_P7.62mm_Horizontal,1,470r or 47k opt,
R6,R_Axial_DIN0207_L6.3mm_D2.5mm_P7.62mm_Horizontal,1,47k opt,
"RV1, RV2",Potentiometer_Bourns_3299Y_Vertical,2,1k,
U1,DIP-16_W7.62mm,1,LTV-847,
U2,DIP-28_W7.62mm,1,MCP23017_SP,
U3,DIP-8_W7.62mm,1,LM393,
"U4, U5",DIP-18_W7.62mm_Socket,2,MIC2981/82YN,
U6,Converter_DCDC_RECOM_R-78E-0.5_THT,1,R-78E5.0-1.0,
U7,DIP-16_W7.62mm,1,MAX232N,
U8,DIP-8_W7.62mm,1,LTV-827,
U9,SOIC-8_3.9x4.9mm_P1.27mm,1,ACS712xLCTR-30A,
